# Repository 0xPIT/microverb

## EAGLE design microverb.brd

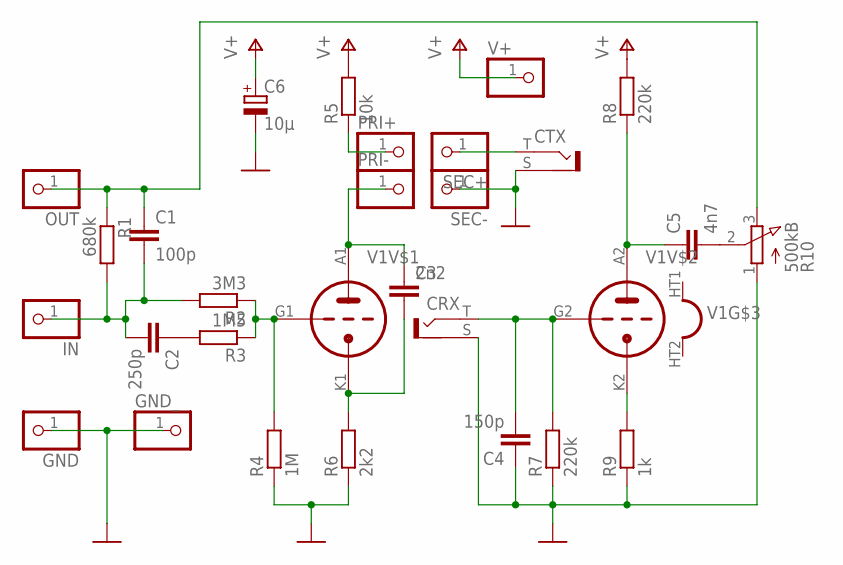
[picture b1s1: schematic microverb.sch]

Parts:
C1: 100p; C1206
C2: 250p; C1206
C3: 2n2; C1206
C4: 150p; C1206
C5: 4n7; C1206
C6: 10µ; E5-10,5
CRX: BTOR1
CTX: BTOR1
GND: PINHD-1X1; 1X01
GND_: PINHD-1X1; 1X01
IN: PINHD-1X1; 1X01
OUT: PINHD-1X1; 1X01
PRI+: PINHD-1X1; 1X01
PRI-: PINHD-1X1; 1X01
R1: 680k; R1206
R2: 3M3; R1206
R3: 1M5; R1206
R4: 1M; R1206
R5: 10k; R2512
R6: 2k2; R1206
R7, R8: 220k; R1206
R9: 1k; R1206
R10: 500kB; 3RP/1610N
SEC+: PINHD-1X1; 1X01
SEC-: PINHD-1X1; 1X01
V1: 6NXX-PIT
V+: PINHD-1X1; 1X01

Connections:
GND: C4.1, C6.-, CRX.S (2), CTX.S (2), GND.1, GND_.1, R4.1, R6.1, R7.1, R9.1, R10.1 (A), SEC-.1
unnamed: C3.2, R6.2, V1.K1 (TK)
unnamed: R2.1, R3.1, R4.2, V1.G1 (TG)
unnamed: C4.2, CRX.T (1), R7.2, V1.G2 (TG)
unnamed: R9.2, V1.K2 (TK)
unnamed: C2.1, R3.2
unnamed: C5.1, R8.1, V1.A2 (TA)
unnamed: PRI+.1, R5.1
unnamed: C3.1, PRI-.1, V1.A1 (TA)
unnamed: CTX.T (1), SEC+.1
unnamed: C1.2, C2.2, IN.1, R1.2, R2.2
unnamed: C5.2, R10.2 (S)
unnamed: C1.1, OUT.1, R1.1, R10.3 (E)
V+: C6.+, R5.2, R8.2, V+.1

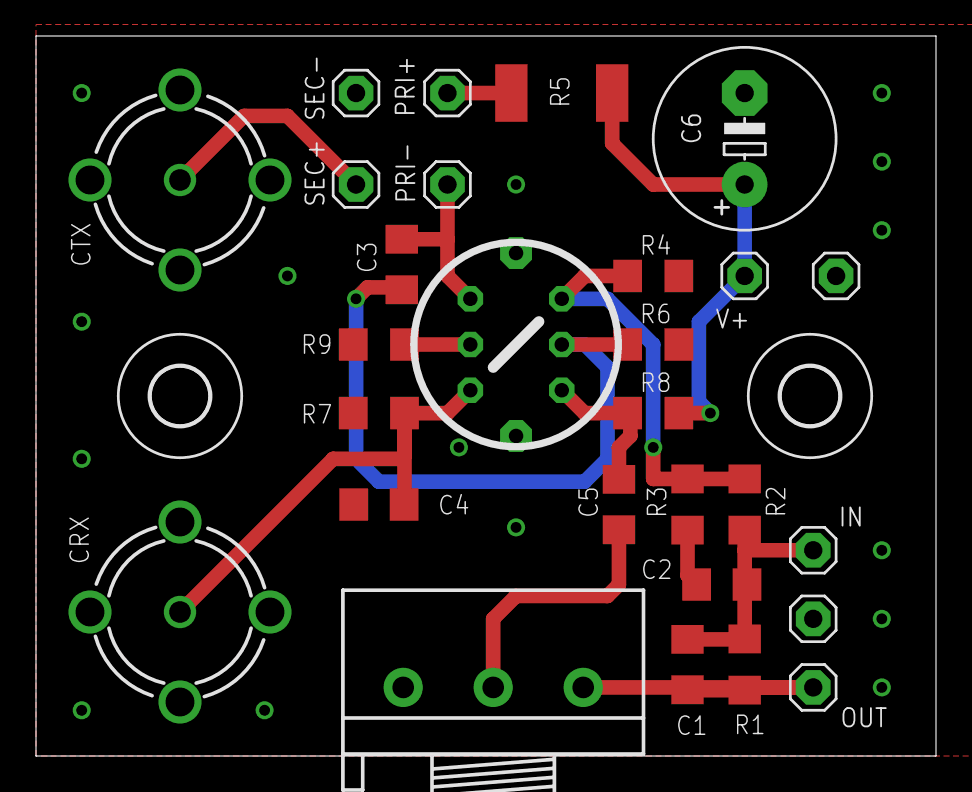
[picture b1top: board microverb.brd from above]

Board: 2 copper layers, 50.0 x 40.0 mm, 30 parts (0 on the bottom side), 14 nets.

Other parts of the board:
U$2, U$3: 3,2

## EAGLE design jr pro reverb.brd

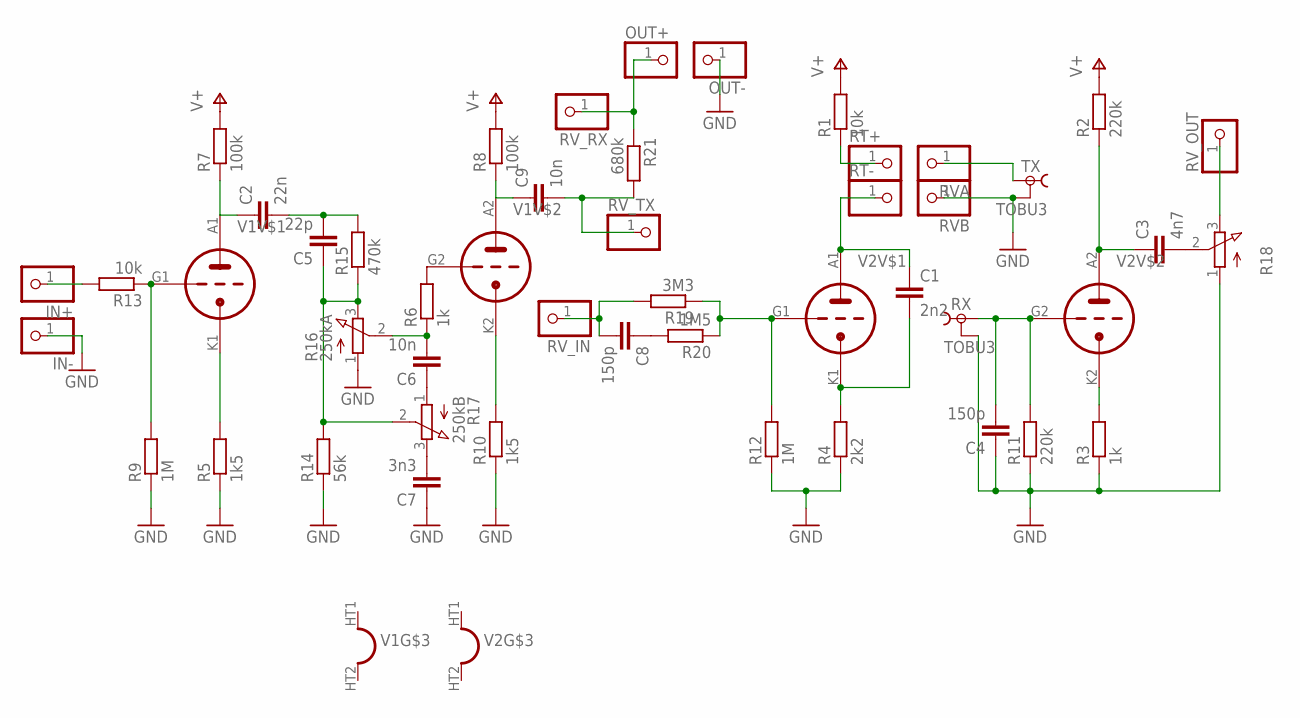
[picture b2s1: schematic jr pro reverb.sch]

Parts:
C1: 2n2; C050-030X075
C2: 22n; C050-045X075
C3: 4n7; C050-045X075
C4, C8: 150p; C050-030X075
C5: 22p; C050-030X075
C6, C9: 10n; C050-045X075
C7: 3n3; C050-045X075
IN+: PINHD-1X1; 1X01
IN-: PINHD-1X1; 1X01
OUT+: PINHD-1X1; 1X01
OUT-: PINHD-1X1; 1X01
R1, R13: 10k; 0207/7
R2, R11: 220k; 0207/7
R3, R6: 1k; 0207/7
R4: 2k2; 0207/7
R5, R10: 1k5; 0207/7
R7, R8: 100k; 0207/7
R9, R12: 1M; 0207/7
R14: 56k; 0207/7
R15: 470k; 0207/7
R16: 250kA; 3RP/1610N
R17: 250kB; 3RP/1610N
R18: 3RP/1610N
R19: 3M3; 0207/7
R20: 1M5; 0207/7
R21: 680k; 0207/7
RT+: PINHD-1X1; 1X01
RT-: PINHD-1X1; 1X01
RVA: PINHD-1X1; 1X01
RVB: PINHD-1X1; 1X01
RV_IN: PINHD-1X1; 1X01
RV_OUT: PINHD-1X1; 1X01
RV_RX: PINHD-1X1; 1X01
RV_TX: PINHD-1X1; 1X01
RX: TOBU3
TX: TOBU3
V1, V2: 6NXX-PIT

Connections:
GND: C4.1, C7.1, IN-.1, OUT-.1, R3.1, R4.1, R5.1, R9.1, R10.1, R11.1, R12.1, R14.1, R16.1 (A), R18.1 (A), RVB.1, RX.2, RX.2@1 (2), RX.2@2 (2), TX.2, TX.2@1 (2), TX.2@2 (2)
unnamed: C1.2, R4.2, V2.K1 (TK)
unnamed: R12.2, R19.1, R20.1, V2.G1 (TG)
unnamed: C4.2, R11.2, RX.1, V2.G2 (TG)
unnamed: R3.2, V2.K2 (TK)
unnamed: C8.1, R20.2
unnamed: C9.1, R8.1, V1.A2 (TA)
unnamed: C2.1, R7.1, V1.A1 (TA)
unnamed: C3.1, R2.1, V2.A2 (TA)
unnamed: R1.1, RT+.1
unnamed: C1.1, RT-.1, V2.A1 (TA)
unnamed: R5.2, V1.K1 (TK)
unnamed: RVA.1, TX.1
unnamed: R10.2, V1.K2 (TK)
unnamed: R9.2, R13.1, V1.G1 (TG)
unnamed: R6.2, V1.G2 (TG)
unnamed: C6.2, R6.1, R16.2 (S)
unnamed: C6.1, R17.1 (A)
unnamed: C5.1, R14.2, R15.1, R16.3 (E), R17.2 (S)
unnamed: OUT+.1, R21.1, RV_RX.1
unnamed: C7.2, R17.3 (E)
unnamed: C2.2, C5.2, R15.2
unnamed: C9.2, R21.2, RV_TX.1
unnamed: C8.2, R19.2, RV_IN.1
unnamed: C3.2, R18.2 (S)
unnamed: R18.3 (E), RV_OUT.1
unnamed: IN+.1, R13.2
V+: R1.2, R2.2, R7.2, R8.2

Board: 2 copper layers, 49 parts (0 on the bottom side), 28 nets, no tracks yet.

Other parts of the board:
U$1, U$2, U$3: 3,2

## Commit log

2015-01-24 initial add
2015-01-24 fix silkscreen
